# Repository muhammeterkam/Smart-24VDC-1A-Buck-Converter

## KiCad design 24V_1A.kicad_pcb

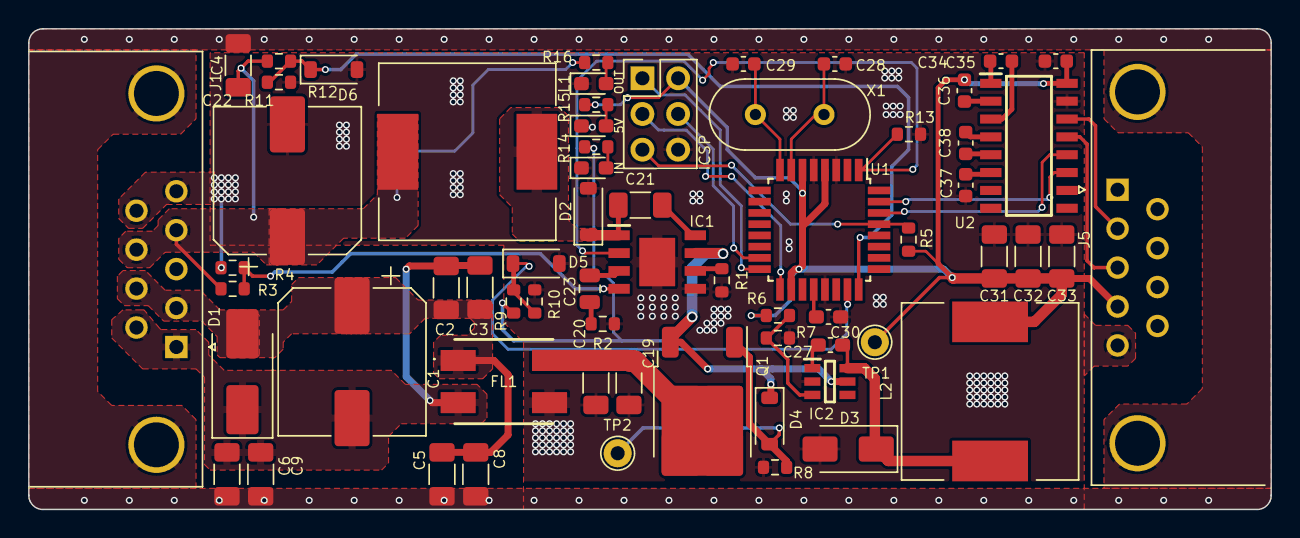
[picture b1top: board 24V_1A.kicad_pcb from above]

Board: 2 copper layers, 88.4 x 34.2 mm, 64 parts (0 on the bottom side), 41 nets.

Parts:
5V: LED; LED_0603_1608Metric_Pad1.05x0.95mm_HandSolder
C1, C22: 100uF; CP_Elec_10x10
C2, C4, C5, C6, C19, C20, C32, C33: 10uF; C_1206_3216Metric_Pad1.33x1.80mm_HandSolder
C3, C8, C9, C21: 100nF; C_1206_3216Metric_Pad1.33x1.80mm_HandSolder
C23: 680pF; C_0805_2012Metric
C27, C30: 100nF; C_0603_1608Metric_Pad1.08x0.95mm_HandSolder
C28, C29: 22pF; C_0603_1608Metric
C31: 22uF; C_1206_3216Metric_Pad1.33x1.80mm_HandSolder
C34, C36, C37, C38: 1uF; C_0603_1608Metric
C35: 10uF; C_0603_1608Metric
D1: SMBJ51CA-HT; D_SMB_Handsoldering
D2, D4: BZT52-C20_R1_00001; D_SOD-123
D3: D; D_SMA
D5, D6: 5V; D_SOD-123
FL1: Filter_EMI_CommonMode; ACM70603012PLTL01
IC1: MPQ4559DN-LF-P; SOIC127P600X170-9N
IC2: HT7463B; SOT95P280X145-6N
ICSP: Conn_02x03_Odd_Even; PinHeader_2x03_P2.54mm_Vertical
IN: LED; LED_0603_1608Metric_Pad1.05x0.95mm_HandSolder
J1, J5: DE9_Receptacle_MountingHoles; DSUB-9_Female_Horizontal_P2.77x2.84mm_EdgePinOffset7.70mm_H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
L1: 15uH; L_12x12mm_H8mm
L2: 47uH; L_12x12mm_H8mm
OUT: LED; LED_0603_1608Metric_Pad1.05x0.95mm_HandSolder
Q1: DMPH6050SK3; TO-252-2
R1, R2: 200k; R_0603_1608Metric
R3: 290k; R_0603_1608Metric
R4, R8, R10, R12, R13: 10k; R_0603_1608Metric
R5, R9: 100k; R_0603_1608Metric
R6: 82k; R_0603_1608Metric
R7: 15k; R_0603_1608Metric
R11: 50k; R_0603_1608Metric
R14: 46k; R_0603_1608Metric
R15: 1k; R_0603_1608Metric
R16: 4.7k; R_0603_1608Metric
TP1, TP2: TestPoint; TestPoint_THTPad_D2.0mm_Drill1.0mm
U1: ATmega328-A; TQFP-32_7x7mm_P0.8mm
U2: MAX232; SOIC127P600X175-16N
X1: 16Mhz; Crystal_HC49-4H_Vertical

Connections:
5V_PRI: C31.2, C32.1, C33.1, C35.1, C36.2, ICSP.2, J5.4, L2.2, R5.1, R6.1, R15.1, TP1.1, U1.4 (VCC), U1.6 (VCC), U1.18 (AVCC), U2.16 (VCC)
GNDPWR: C4.2, C5.1, C6.2, C8.1, C9.2, J1.0 (PAD), J5.0 (PAD)
MCU_CONV_EN: IC1.2 (EN), R13.1, U1.1 (PD3)
MCU_RX: U1.30 (PD0), U2.12 (R1OUT)
MCU_TX: U1.31 (PD1), U2.11 (T1IN)
MISO: ICSP.1, U1.16 (PB4)
MOSI: ICSP.4, U1.15 (PB3)
unnamed: C23.1, R2.2
unnamed: C21.1, D2.1 (K), IC1.1 (SW), L1.2
unnamed: C30.2, D3.1 (K), IC2.6 (SW), L2.1
unnamed: D4.2 (A), Q1.1 (G), R8.1, TP2.1
unnamed: IN.2 (A), R14.2
unnamed: 5V.2 (A), R15.2
unnamed: OUT.2 (A), R16.2
unnamed: C21.2, IC1.8 (BST)
unnamed: C23.2, IC1.3 (COMP)
unnamed: IC1.6 (FREQ), R1.1
unnamed: C30.1, IC2.1 (CB)
unnamed: IC2.3 (FB), R6.2, R7.1
unnamed: C27.2, U1.20 (AREF)
unnamed: C34.2, U2.1 (C1+)
unnamed: C34.1, U2.3 (C1-)
unnamed: C38.1, U2.4 (C2+)
unnamed: C38.2, U2.5 (C2-)
unnamed: J5.3, U2.13 (R1IN)
unnamed: J5.2, U2.14 (T1OUT)
unnamed: C36.1, U2.2 (VS+)
unnamed: C37.1, U2.6 (VS-)
PWR_IN: C1.1, C2.1, C3.1, C5.2, C8.2, D1.2 (A2), FL1.1, J1.2, J1.7
PWR_IN_FLT: C19.1, C20.1, FL1.2, Q1.2 (D)
PWR_IN_RP: D4.1 (K), IC1.7 (VIN), IC2.5 (VIN), Q1.3 (S), R9.1, R14.1
PWR_IN_RP_FB: D5.1 (K), R9.2, R10.1, U1.23 (PC0)
PWR_IN_RTN: 5V.1 (K), C19.2, C20.2, C22.2, C27.1, C28.2, C29.2, C31.1, C32.2, C33.2, C35.2, C37.2, D2.2 (A), D3.2 (A), D5.2 (A), D6.2 (A), FL1.4, IC1.5 (GND), IC1.9 (EP), IC2.2 (GND), ICSP.6, IN.1 (K), J1.5, J1.9, J5.5, OUT.1 (K), R1.2, R2.1, R4.1, R7.2, R8.2, R10.2, R12.2, R13.2, U1.3 (GND), U1.5 (GND), U1.21 (GND), U2.15 (GND)
PWR_IN_RTN_PRI: C1.2, C2.2, C3.2, C6.1, C9.1, D1.1 (A1), FL1.3, J1.1, J1.6
PWR_OUT: C4.1, C22.1, J1.4, J1.8, L1.1, R3.1, R11.1, R16.1
PWR_OUT_FB: D6.1 (K), R11.2, R12.1, U1.24 (PC1)
REG_FB: IC1.4 (FB), R3.2, R4.2
RESET: ICSP.5, R5.2, U1.29 (~RESET/PC6)
SCK: ICSP.3, U1.17 (PB5)
XTAL1: C28.1, U1.7 (XTAL1/PB6), X1.2
XTAL2: C29.1, U1.8 (XTAL2/PB7), X1.1

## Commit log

2024-08-11 initial
2024-08-11 README.md
